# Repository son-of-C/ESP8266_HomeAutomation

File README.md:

# ESP8266_HomeAutomation

Required : KiCad software to open this files.

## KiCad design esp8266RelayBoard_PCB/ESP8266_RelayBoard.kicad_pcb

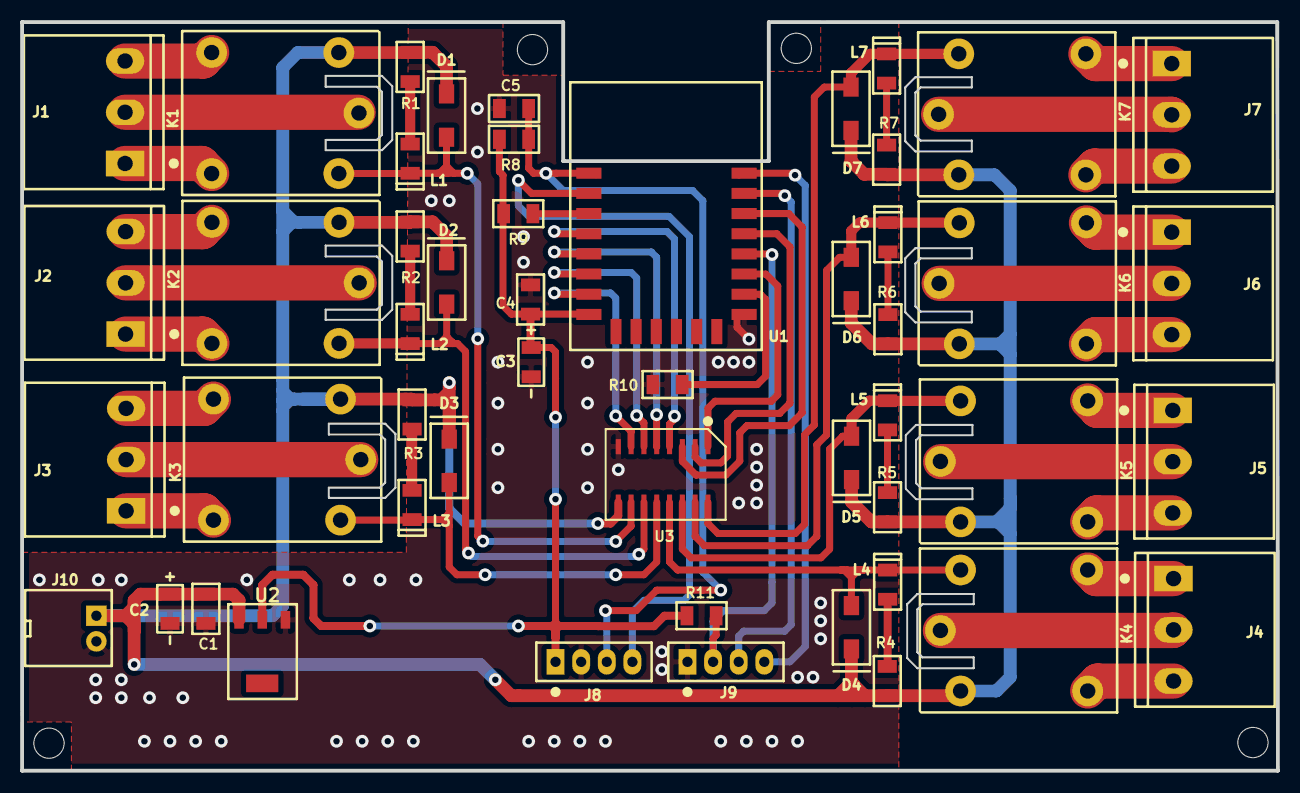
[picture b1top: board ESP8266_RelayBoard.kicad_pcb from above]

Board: 2 copper layers, 124.5 x 74.2 mm, 54 parts (0 on the bottom side), 52 nets.

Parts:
C1, C4, C5: 100nF; 1206_C
C2, C3: 10uF16V; 1206_tanta
D1, D2, D3, D4, D5, D6, D7: 1N4148; ZenerDiode_S1M
J1, J2, J3, J4, J5, J6, J7: Screw_Terminal_01x03; TerminalBlock_bornier-3_P5.08mm
J8, J9: Conn_01x04; Socket_Strip_Straight_1x04_Pitch2.54mm
J10: Conn_01x02; 2PinJST_Connector
K1, K2, K3, K4, K5, K6, K7: G5LE-1; Relay12V
L1, L2, L3, L4, L5, L6, L7: LED_Small; 1206_LED
MH1, MH2, MH3, MH4: MountingHole; MountNPTH_3.0mm
R1, R2, R3, R4, R5, R6, R7: 2.2K; 1206_R
R8, R9, R10, R11: 10K; 1206_R
U1: ESP8266-12E; ESP-12E_SMD
U2: AMS1117-3.3; LM1117_SOT_4pin
U3: ULN2003A; SOP-16_SYN510R

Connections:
3.3VDC: C3.1, C4.1, J8.1, R8.1, R9.2, R11.1, U1.8, U2.2
+12VDC: C1.1, C2.1, D1.1, D2.1, D3.1, D4.1, D5.1, D6.1, D7.1, J10.1, K1.2, K2.2, K3.2, K4.2, K5.2, K6.2, K7.2, R1.1, R2.1, R3.1, R4.1, R5.1, R6.1, R7.1, U2.3, U3.9
ADC0: J8.4, U1.2
COMMON1: J1.2, K1.3
COMMON2: J2.2, K2.3
COMMON3: J3.2, K3.3
COMMON4: J4.2, K4.3
COMMON5: J5.2, K5.3
COMMON6: J6.2, K6.3
COMMON7: J7.2, K7.3
GND: C1.2, C2.2, C3.2, C4.2, C5.2, J8.2, J9.1, J10.2, R10.1, U1.15, U2.1, U3.8
GPIO_0: J9.2, R11.2, U1.18
GPIO_2: U1.17, U3.1
GPIO_4: U1.19, U3.2
GPIO_5: U1.20, U3.3
GPIO_12: U1.6, U3.6
GPIO_13: U1.7, U3.7
GPIO_14: U1.5, U3.5
GPIO_16: U1.4, U3.4
NC1: J1.1, K1.4
NC2: J2.1, K2.4
NC3: J3.1, K3.4
NC4: J4.1, K4.4
NC5: J5.1, K5.4
NC6: J6.1, K6.4
NC7: J7.1, K7.4
NO1: J1.3, K1.5
NO2: J2.3, K2.5
NO3: J3.3, K3.5
NO4: J4.3, K4.5
NO5: J5.3, K5.5
NO6: J6.3, K6.5
NO7: J7.3, K7.5
unnamed: L1.2, R1.2
unnamed: L2.2, R2.2
unnamed: L3.2, R3.2
unnamed: L4.2, R4.2
unnamed: L5.2, R5.2
unnamed: L6.2, R6.2
unnamed: L7.2, R7.2
unnamed: R9.1, U1.3
unnamed: R10.2, U1.16
RL1: D1.2, K1.1, L1.1, U3.10
RL2: D2.2, K2.1, L2.1, U3.11
RL3: D3.2, K3.1, L3.1, U3.12
RL4: D4.2, K4.1, L4.1, U3.13
RL5: D5.2, K5.1, L5.1, U3.14
RL6: D6.2, K6.1, L6.1, U3.15
RL7: D7.2, K7.1, L7.1, U3.16
RST: C5.1, J8.3, R8.2, U1.1
RX: J9.3, U1.21
TX: J9.4, U1.22

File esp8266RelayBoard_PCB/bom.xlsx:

Component Count: | 53
Ref | Qnty | Value | Type
C2, C3, | 2 | 10uF16V | 1206 SMD | 4688
C4, C1, C5, | 3 | 100nF | 1206 SMD | 3942
D1, D2, D3, D5, D4, D6, D7, | 7 | 1N4148 | SMD | 4418
J1, J2, J4, J3, J7, J5, J6, | 7 | Screw_Terminal_01x03 | Relay Connector
J9, J8, | 2 | Conn_01x04 | male header
J10, | 1 | Conn_01x02 | male header
K1, K2, K3, K5, K4, K6, K7, | 7 | G5LE-1 | relay
L1, L2, L3, L5, L4, L6, L7, | 7 | LED_Small | 1206 SMD
R1, R2, R3, R5, R4, R6, R7, | 7 | 2.2K | 1206 SMD
R10, R11, R9, R8, | 4 | 10K | 1206 SMD | 4068
U1, | 1 | ESP8266-12E | chip | 6182
U2, | 1 | AMS1117-3.3 | sot-23 | 4004
U3, | 1 | ULN2003A | discreate | 5293
FAN CONTROL COMPONENT
 | 1 | DIMMER | SUNROM | 1289
 | 2 | 100nf 400V | SHANTINATH
 | 4 | 470k 1W | SHANTINATH
 | 2 | 1K
 | 2 | 10K
 | 2 | 220R
 | 2 | 470R
 | 1 | PCB ETCHING | SHANTINATH
 | 1 | PCB | SHANTINATH
 | 1 | PCB DRILL
 | 1 | USB TO TTL CABLE | SHANTINATH
 |  | ESP PRICE AT SHANTINATH

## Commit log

2021-02-07 Esp8266_RelayBoard
    We can control AC appliances using this board
